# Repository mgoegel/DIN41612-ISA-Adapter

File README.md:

# DIN41612 to ISA Adapter

Here, I created a KiCad 6 Project.

The goal was, to create a PCB for debugging/testing of robotron EC1834 addon Boards on Standard XT PCs.

[Schematics](DIN41612-ISA/DIN41612-ISA.pdf)

Below is the Bill of Materials for the board:

```
Ref(s)      Value                               Mouser P/N
-------------------------------------------------------------------------------
J1          DIN 41612 Type R a+b+c 3x32 PINs    649-8693968837V1LF  
            (96 PINs) Receptacles
J2, J3      13x1 header                         538-22-28-4200 (See Note 1)
J4, J5      31x1 header                         538-22-28-4200 (See Note 1)
BRACKET     Keystone 9202 ISA bracket           534-9202
SCREWS      4-40 x 1/4" machine screw           534-9301
```

But the 
Note 1: Order a 20 (or greater) breakaway header, break into the required lengths.

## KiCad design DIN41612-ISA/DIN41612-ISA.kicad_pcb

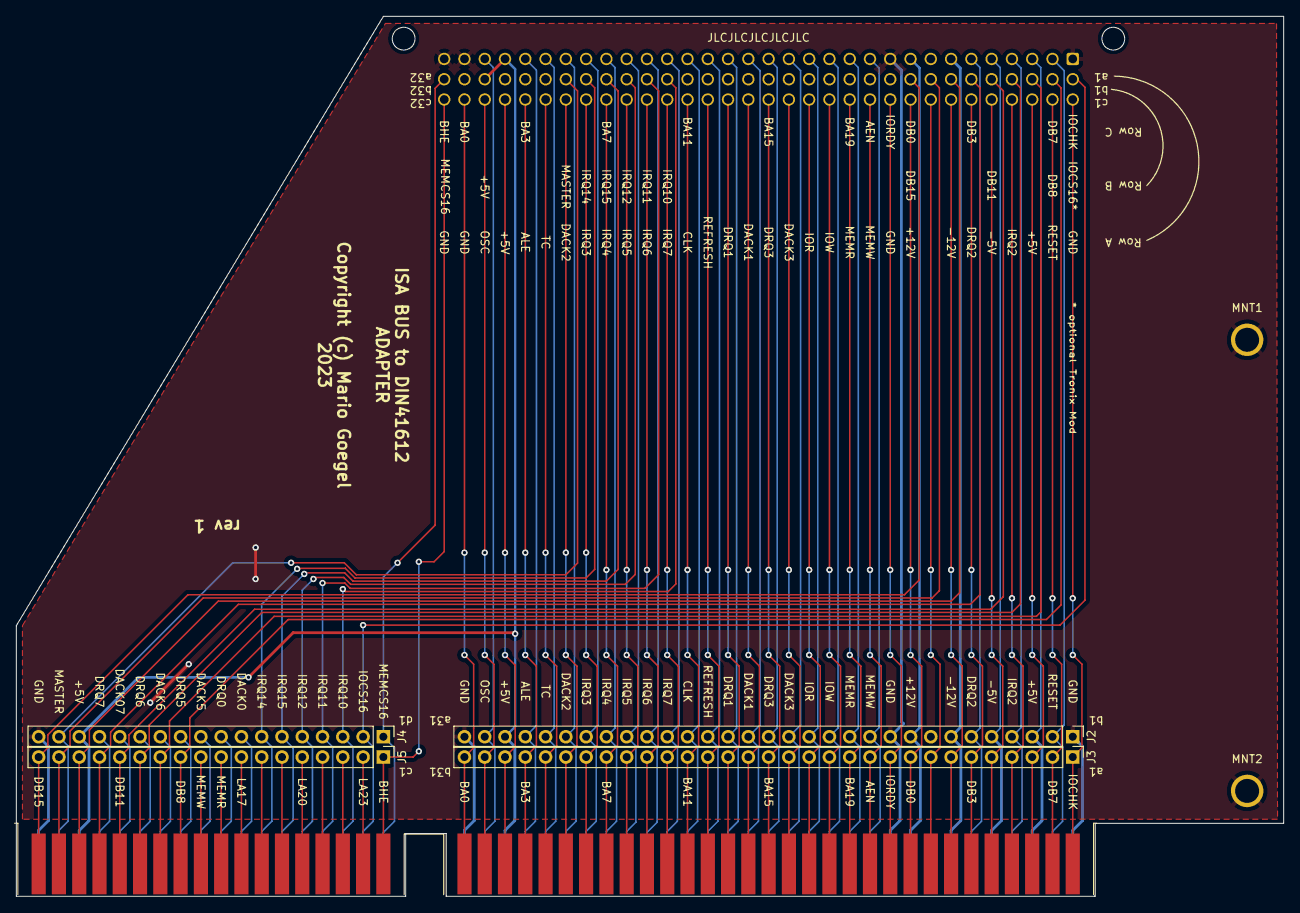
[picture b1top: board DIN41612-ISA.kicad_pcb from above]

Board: 2 copper layers, 158.8 x 110.2 mm, 8 parts (1 on the bottom side), 92 nets.

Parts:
J1: Bus_ISA_16bit; BUS_AT
J2, J3: Conn_01x31; PinHeader_1x31_P2.54mm_Vertical
J4, J5: Conn_01x18; PinHeader_1x18_P2.54mm_Vertical
MNT1, MNT2: MountingHole_3mm_Pad
U1: BUS_EC1834_16Bit_RAMCARD; DIN41612_C_3x32_Male_Horizontal_THT_PressFit

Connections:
/+5V: J1.3 (+5V), J1.29 (VCC), J1.78 (+5V), J2.3, J2.29, J4.16, U1.a3 (+5V), U1.a29 (VCC), U1.b30 (+5V)
/+12V: J1.9 (+12V), J2.9, U1.a9 (+12V)
/-5V: J1.5 (-5V), J2.5, U1.a5 (-5V)
/-12V: J1.7 (-12V), J2.7, U1.a7 (-12V)
/AEN: J1.42 (AEN), J3.11, U1.c11 (AEN)
/ALE: J1.28 (ALE), J2.28, U1.a28 (ALE)
/BA0: J1.62 (BA00), J3.31, U1.c31 (BA00)
/BA1: J1.61 (BA01), J3.30, U1.c30 (BA01)
/BA2: J1.60 (BA02), J3.29, U1.c29 (BA02)
/BA3: J1.59 (BA03), J3.28, U1.c28 (BA03)
/BA4: J1.58 (BA04), J3.27, U1.c27 (BA04)
/BA5: J1.57 (BA05), J3.26, U1.c26 (BA05)
/BA6: J1.56 (BA06), J3.25, U1.c25 (BA06)
/BA7: J1.55 (BA07), J3.24, U1.c24 (BA07)
/BA8: J1.54 (BA08), J3.23, U1.c23 (BA08)
/BA9: J1.53 (BA09), J3.22, U1.c22 (BA09)
/BA10: J1.52 (BA10), J3.21, U1.c21 (BA10)
/BA11: J1.51 (BA11), J3.20, U1.c20 (BA11)
/BA12: J1.50 (BA12), J3.19, U1.c19 (BA12)
/BA13: J1.49 (BA13), J3.18, U1.c18 (BA13)
/BA14: J1.48 (BA14), J3.17, U1.c17 (BA14)
/BA15: J1.47 (BA15), J3.16, U1.c16 (BA15)
/BA16: J1.46 (BA16), J3.15, U1.c15 (BA16)
/BA17: J1.45 (BA17), J3.14, U1.c14 (BA17)
/BA18: J1.44 (BA18), J3.13, U1.c13 (BA18)
/BA19: J1.43 (BA19), J3.12, U1.c12 (BA19)
/BHE: J1.81 (SBHE), J5.1, U1.c32 (~BHE)
/CLK: J1.20 (CLK), J2.20, U1.a20 (CLK)
/DACK1: J1.17 (~DACK1), J2.17, U1.a17 (~DACK1)
/DACK2: J1.26 (~DACK2), J2.26, U1.a26 (~DACK2)
/DACK3: J1.15 (~DACK3), J2.15, U1.a15 (~DACK3)
/DB0: J1.40 (DB0), J3.9, U1.c9 (DB0)
/DB1: J1.39 (DB1), J3.8, U1.c8 (DB1)
/DB2: J1.38 (DB2), J3.7, U1.c7 (DB2)
/DB3: J1.37 (DB3), J3.6, U1.c6 (DB3)
/DB4: J1.36 (DB4), J3.5, U1.c5 (DB4)
/DB5: J1.35 (DB5), J3.4, U1.c4 (DB5)
/DB6: J1.34 (DB6), J3.3, U1.c3 (DB6)
/DB7: J1.33 (DB7), J3.2, U1.c2 (DB7)
/DB8: J1.91 (D8), J5.11, U1.b2 (DB8)
/DB9: J1.92 (D9), J5.12, U1.b3 (DB9)
/DB10: J1.93 (D10), J5.13, U1.b4 (DB10)
/DB11: J1.94 (D11), J5.14, U1.b5 (DB11)
/DB12: J1.95 (D12), J5.15, U1.b6 (DB12)
/DB13: J1.96 (D13), J5.16, U1.b7 (DB13)
/DB14: J1.97 (D14), J5.17, U1.b8 (DB14)
/DB15: J1.98 (D15), J5.18, U1.b9 (DB15)
/DRQ1: J1.18 (DRQ1), J2.18, U1.a18 (DRQ1)
/DRQ2: J1.6 (DRQ2), J2.6, U1.a6 (DRQ2)
/DRQ3: J1.16 (DRQ3), J2.16, U1.a16 (DRQ3)
/GND: J1.1 (GND), J1.10 (GND), J1.31 (GND), J1.80 (GND), J2.1, J2.10, J2.31, J4.18, MNT1.1, MNT2.1, U1.a1 (GND), U1.a10 (GND), U1.a31 (GND), U1.a32 (GND)
/IOCHK: J1.32 (IO), J3.1, U1.c1 (~IOCHCK)
/IOCS16: J1.64 (~IOCS16), J4.2, U1.b1 (~IOCS16)
/IOR: J1.14 (~IOR), J2.14, U1.a14 (~IOR)
/IORDY: J1.41 (IO_READY), J3.10, U1.c10 (IOCHRDY)
/IOW: J1.13 (~IOW), J2.13, U1.a13 (~IOW)
/IRQ2: J1.4 (IRQ2), J2.4, U1.a4 (IRQ2)
/IRQ3: J1.25 (IRQ3), J2.25, U1.a25 (IRQ3)
/IRQ4: J1.24 (IRQ4), J2.24, U1.a24 (IRQ4)
/IRQ5: J1.23 (IRQ5), J2.23, U1.a23 (IRQ5)
/IRQ6: J1.22 (IRQ6), J2.22, U1.a22 (IRQ6)
/IRQ7: J1.21 (IRQ7), J2.21, U1.a21 (IRQ7)
/IRQ10: J1.65 (IRQ10), J4.3, U1.b21 (IRQ10)
/IRQ11: J1.66 (IRQ11), J4.4, U1.b22 (IRQ11)
/IRQ12: J1.67 (IRQ12), J4.5, U1.b23 (IRQ12)
/IRQ14: J1.69 (IRQ14), J4.7, U1.b25 (IRQ14)
/IRQ15: J1.68 (IRQ15), J4.6, U1.b24 (IRQ15)
/LA17: J1.88 (LA17), J5.8
/LA18: J1.87 (LA18), J5.7
/LA19: J1.86 (LA19), J5.6
/LA20: J1.85 (LA20), J5.5
/LA21: J1.84 (LA21), J5.4
/LA22: J1.83 (LA22), J5.3
/LA23: J1.82 (LA23), J5.2
/MASTER: J1.79 (MASTER), J4.17, U1.b26 (~MASTER)
/MEMCS16: J1.63 (~MEMCS16), J4.1, U1.b32 (~MEMCS16)
/MEMR: J1.12 (~SMEMR), J2.12, U1.a12 (~MEMR)
/MEMR2: J1.89 (~MEMR), J5.9
/MEMW: J1.11 (~SMEMW), J2.11, U1.a11 (~MEMW)
/MEMW2: J1.90 (~MEMW), J5.10
/OSC: J1.30 (OSC), J2.30, U1.a30 (OSC)
/REFR: J1.19 (~REFRESH), J2.19, U1.a19 (~DACK0)
/RESET: J1.2 (RESET), J2.2, U1.a2 (RESET)
/TC: J1.27 (TC), J2.27, U1.a27 (TC)
unnamed: J1.70 (~DACK0), J4.8
unnamed: J1.71 (DRQ0), J4.9
unnamed: J1.72 (~DACK5), J4.10
unnamed: J1.73 (DRQ5), J4.11
unnamed: J1.74 (~DACK6), J4.12
unnamed: J1.75 (DRQ6), J4.13
unnamed: J1.76 (~DACK7), J4.14
unnamed: J1.77 (DRQ7), J4.15

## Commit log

2023-06-06 added README

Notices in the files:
DIN41612-ISA/DIN41612-ISA.kicad_pcb:
Copyright (c) Mario Goegel
